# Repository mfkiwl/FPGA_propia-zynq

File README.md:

# FPGA_propia
 En este repositorio se subirán los ficheros que permitirán crear una FPGA basada en Zynq-7000

Todo el desarrollo está hecho con KiCad (software libre) para que cualquiera pueda replicarla o mejorarla a su gusto con los ficheros que se van a publicar

## Libreria
El fichero tiene una librería llamada 'Zynq-7000' en la que está el symbol de un XC7Z010 del cual se implementará la versión CLG400 (400 pines en formato de soldadura BGA) 
## XC7Z010
El símbolo consta de 9 partes, de las que se va a describir su selección a continuación
### - _Símbolo A_

En este símbolo se reflejan los pines de referencia, además de los pines de depuración TMS, TCK, TDI y TDO. Estos pines pueden necesitar de un cable depurar para cargar el programa o de un USB OTG, que permita evitar tener que usar un cable depurador.

### - _Símbolo B_

En este símbolo se reflejan los pines que no tienen conexión

### - _Símbolo c_

En este símbolo se reflejan los pines de entrada/salida que se podrán configurar como se quiera

### - _Símbolo D_

En este símbolo se reflejan los pines de entrada/salida que se podrán configurar como se quiera

### - _Símbolo E_

En este símbolo se reflejan los pines que van a ir a la/las memoria ram. A los pines de la ram se pueden unir varias memorias para aumentar su tamaño.

### - _Símbolo F_

En este símbolo se reflejan los pines MIO

### - _Símbolo G_

En este símbolo se reflejan los pines MIO continuación de los anteriores

### - _Símbolo H_

En este símbolo se reflejan las alimentaciones de cada parte del integrado. Hay que tener en cuenta que cada parte tiene una alimentación distinta, la VCCO_BRAM y los VCCO_PINT de 1V, los VCCO_MIO 3.3V, los VCCO_DDR de 1.35V y los VCCAUX y los VCCPAUX de 1.8V

### - _Símbolo I_

En este símbolo se reflejan las masas de todo el integrado. Todas las masas van unidas a mismo punto.

### - *Formato del integrado*

En esta imagen se refleja como es el integrado CLG400 de 400 pines(20x20) para BGA

*** Toda la documentación del frabicante se puede obtener del siguiente enlace: ***
https://www.xilinx.com/support/documentation/user_guides/ug865-Zynq-7000-Pkg-Pinout.pdf

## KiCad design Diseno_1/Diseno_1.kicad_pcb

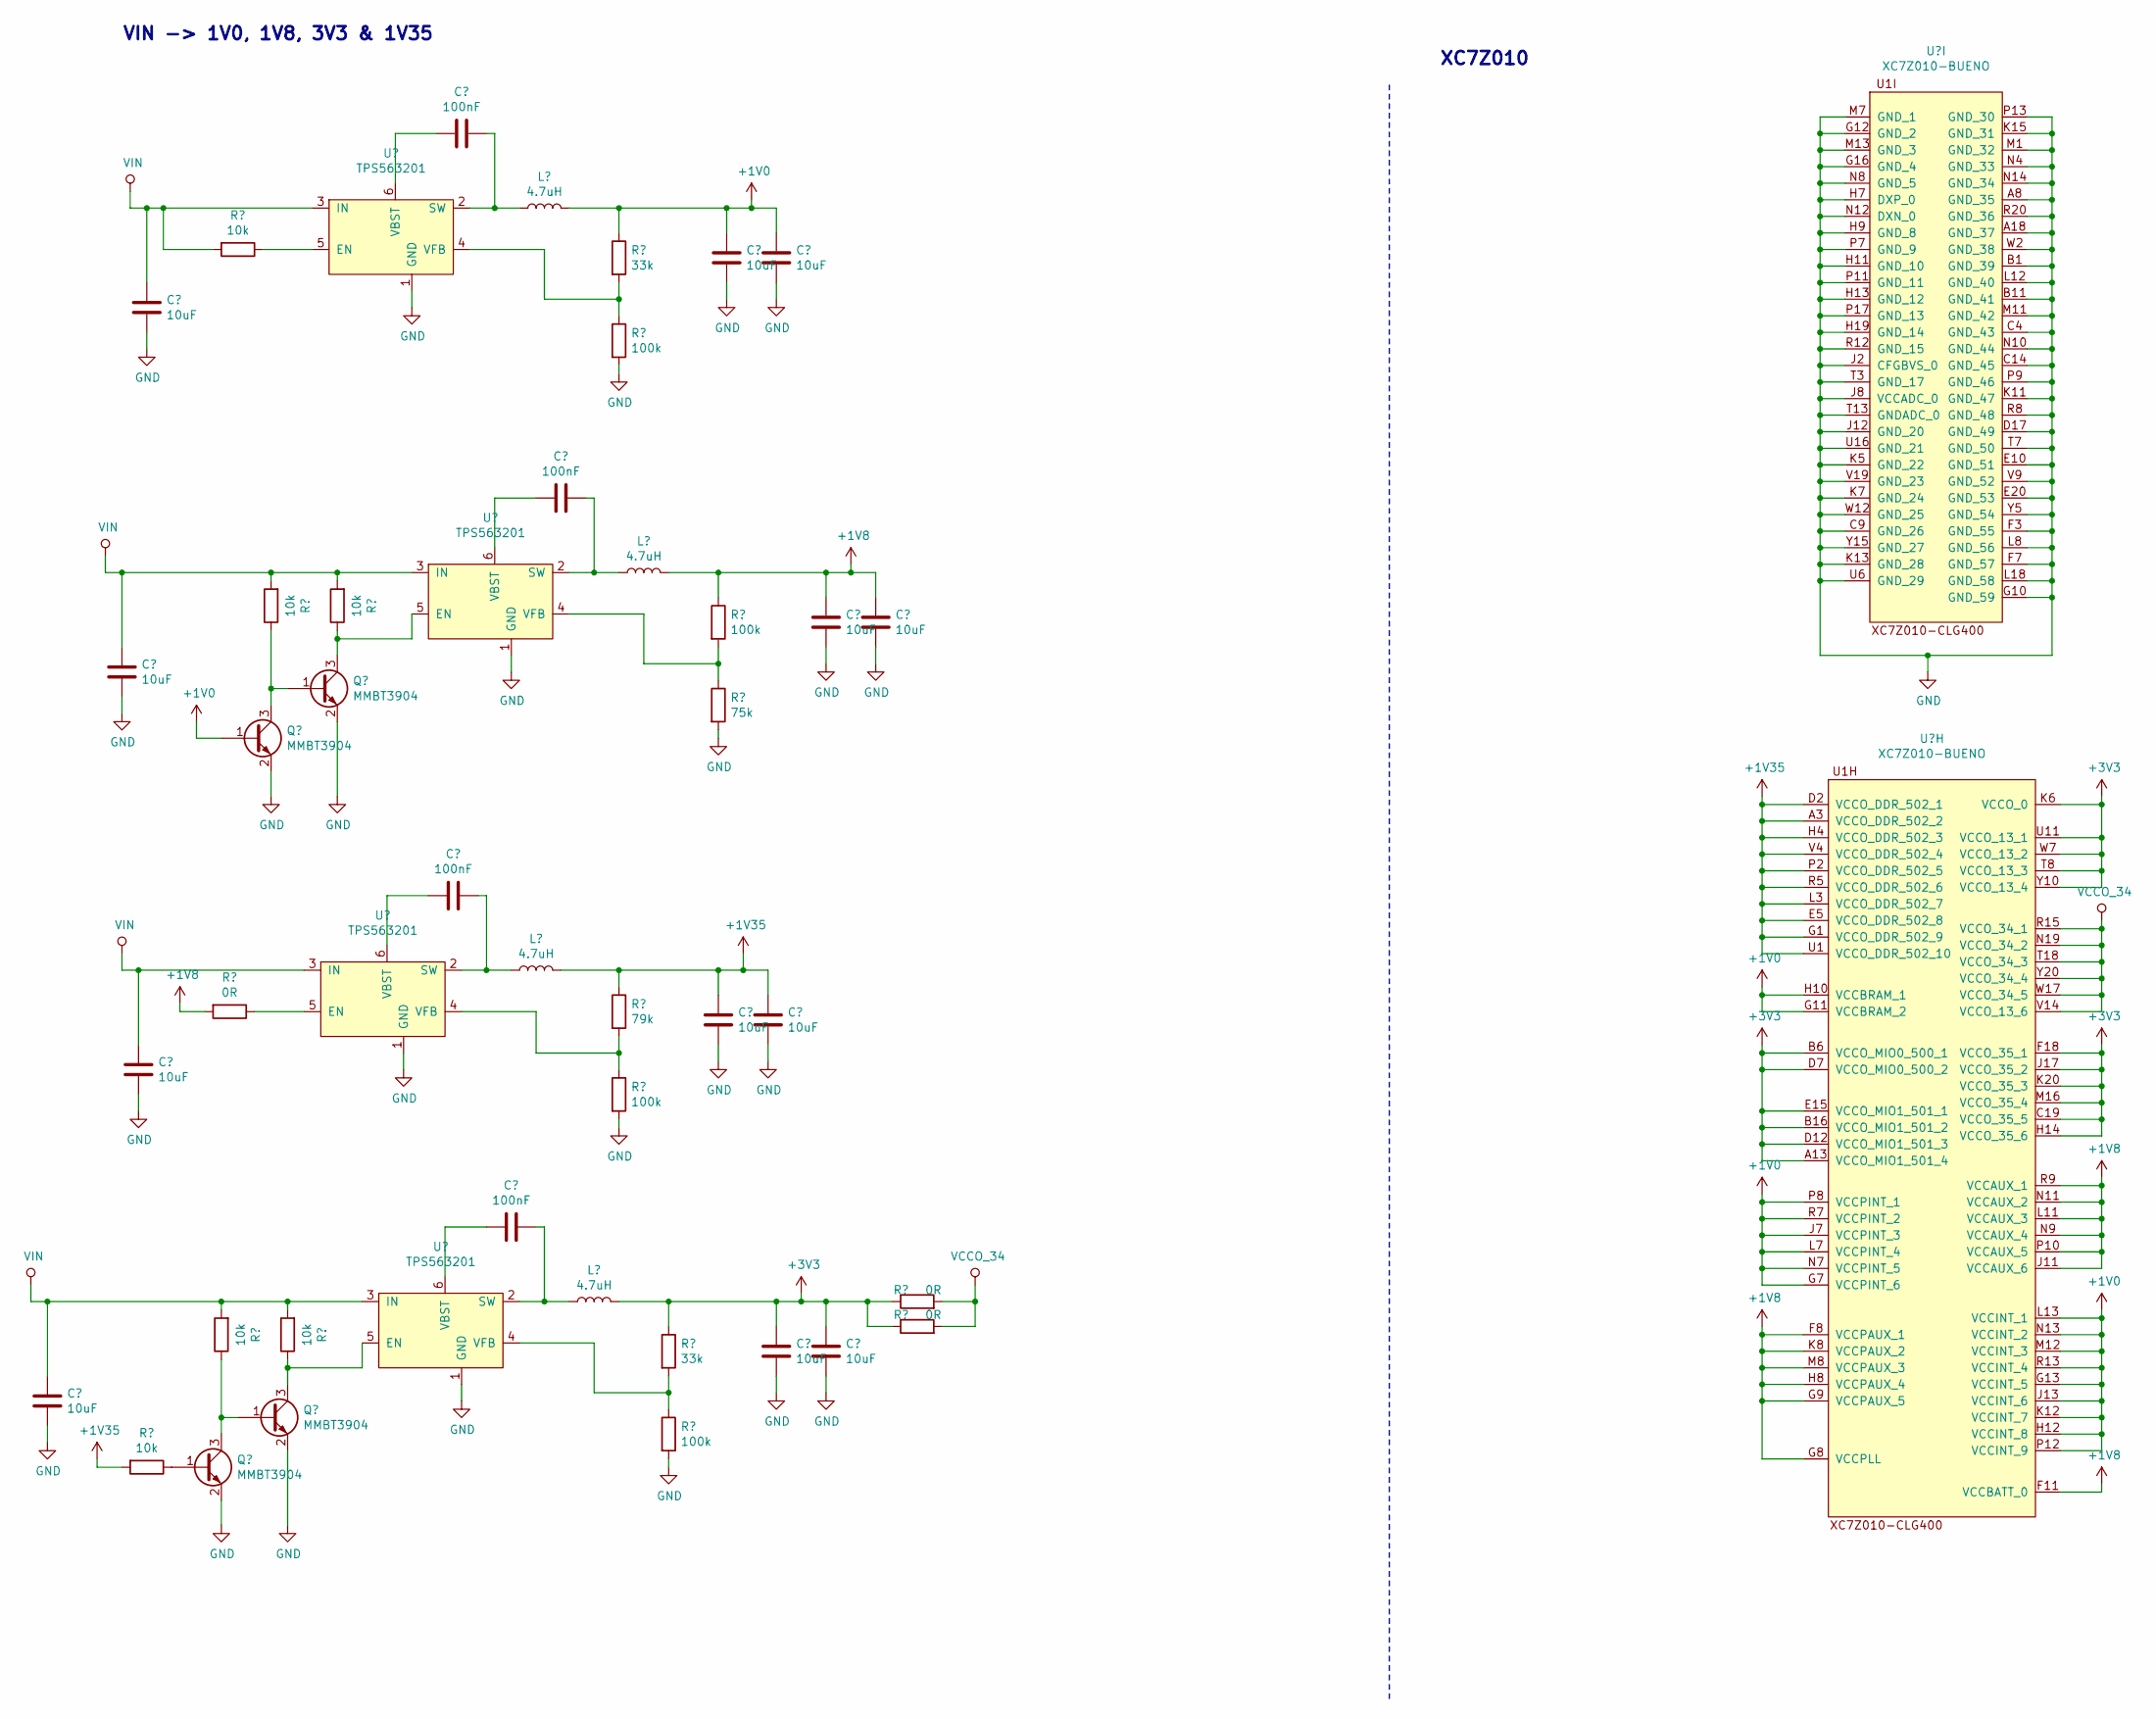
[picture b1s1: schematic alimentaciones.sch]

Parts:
C1, C2, C3, C4, C9, C10, C11, C12, C13, C14, C15, C16: 10uF; C_0805_2012Metric
C5, C6, C7, C8: 100nF; C_0805_2012Metric
L1, L2, L3, L4: 4.7uH; L_0805_2012Metric
Q1, Q2, Q3, Q4: MMBT3904; SOT-23
R1, R2, R4, R5, R6, R7: 10k; R_0805_2012Metric
R3, R16, R17: 0R; R_0805_2012Metric
R8, R12: 33k; R_0805_2012Metric
R9, R11, R13, R14: 100k; R_0805_2012Metric
R10: 79k; R_0805_2012Metric
R15: 75k; R_0805_2012Metric
U1, U2, U3, U4: TPS563201
U5: XC7Z010-BUENO; BGA-400_20x20_17.0x17.0mm

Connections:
+1V0: C10.1, C12.1, L2.2, Q2.1 (B), R8.1, U5.G7 (VCCPINT_6), U5.G11 (VCCBRAM_2), U5.G13 (VCCINT_5), U5.H10 (VCCBRAM_1), U5.H12 (VCCINT_8), U5.J7 (VCCPINT_3), U5.J13 (VCCINT_6), U5.K12 (VCCINT_7), U5.L7 (VCCPINT_4), U5.L13 (VCCINT_1), U5.M12 (VCCINT_3), U5.N7 (VCCPINT_5), U5.N13 (VCCINT_2), U5.P8 (VCCPINT_1), U5.P12 (VCCINT_9), U5.R7 (VCCPINT_2), U5.R13 (VCCINT_4)
+1V8: C14.1, C16.1, L4.2, R3.2, R14.1, U5.F8 (VCCPAUX_1), U5.F11 (VCCBATT_0), U5.G8 (VCCPLL), U5.G9 (VCCPAUX_5), U5.H8 (VCCPAUX_4), U5.J11 (VCCAUX_6), U5.K8 (VCCPAUX_2), U5.L11 (VCCAUX_3), U5.M8 (VCCPAUX_3), U5.N9 (VCCAUX_4), U5.N11 (VCCAUX_2), U5.P10 (VCCAUX_5), U5.R9 (VCCAUX_1); also elsewhere on the board
+1V35: C9.1, C11.1, L1.2, R1.2, R10.1, U5.A3 (VCCO_DDR_502_2), U5.D2 (VCCO_DDR_502_1), U5.E5 (VCCO_DDR_502_8), U5.G1 (VCCO_DDR_502_9), U5.H4 (VCCO_DDR_502_3), U5.L3 (VCCO_DDR_502_7), U5.P2 (VCCO_DDR_502_5), U5.R5 (VCCO_DDR_502_6), U5.U1 (VCCO_DDR_502_10), U5.V4 (VCCO_DDR_502_4); also elsewhere on the board
/Entradas y Salidas/BANK34_N17: U5.N17 (IO_L23P_T3_34); also elsewhere on the board
/Entradas y Salidas/BANK34_N18: U5.N18 (IO_L13P_T2_MRCC_34); also elsewhere on the board
/Entradas y Salidas/BANK34_N20: U5.N20 (IO_L14P_T2_SRCC_34); also elsewhere on the board
/Entradas y Salidas/BANK34_P14: U5.P14 (IO_L6P_T0_34); also elsewhere on the board
/Entradas y Salidas/BANK34_P15: U5.P15 (IO_L24P_T3_34); also elsewhere on the board
/Entradas y Salidas/BANK34_P16: U5.P16 (IO_L24N_T3_34); also elsewhere on the board
/Entradas y Salidas/BANK34_P18: U5.P18 (IO_L23N_T3_34); also elsewhere on the board
/Entradas y Salidas/BANK34_P19: U5.P19 (IO_L13N_T2_MRCC_34); also elsewhere on the board
/Entradas y Salidas/BANK34_P20: U5.P20 (IO_L14N_T2_SRCC_34); also elsewhere on the board
/Entradas y Salidas/BANK34_R14: U5.R14 (IO_L6N_T0_VREF_34); also elsewhere on the board
/Entradas y Salidas/BANK34_R16: U5.R16 (IO_L19P_T3_34); also elsewhere on the board
/Entradas y Salidas/BANK34_R17: U5.R17 (IO_L19N_T3_VREF_34); also elsewhere on the board
/Entradas y Salidas/BANK34_R18: U5.R18 (IO_L20N_T3_34); also elsewhere on the board
/Entradas y Salidas/BANK34_R19: U5.R19 (IO_0_34); also elsewhere on the board
/Entradas y Salidas/BANK34_T10: U5.T10 (IO_L1N_0_34); also elsewhere on the board
/Entradas y Salidas/BANK34_T11: U5.T11 (IO_L1P_T0_34); also elsewhere on the board
/Entradas y Salidas/BANK34_T12: U5.T12 (IO_L2P_T0_34); also elsewhere on the board
/Entradas y Salidas/BANK34_T14: U5.T14 (IO_l5P_T0_34); also elsewhere on the board
/Entradas y Salidas/BANK34_T15: U5.T15 (IO_L5N_T0_34); also elsewhere on the board
/Entradas y Salidas/BANK34_T16: U5.T16 (IO_L9P_T1_DQS_34); also elsewhere on the board
/Entradas y Salidas/BANK34_T17: U5.T17 (IO_L20P_T3_34); also elsewhere on the board
/Entradas y Salidas/BANK34_T19: U5.T19 (IO_25_34); also elsewhere on the board
/Entradas y Salidas/BANK34_T20: U5.T20 (IO_L15P_T2_DQS_34); also elsewhere on the board
/Entradas y Salidas/BANK34_U12: U5.U12 (IO_L2N_T0_34); also elsewhere on the board
/Entradas y Salidas/BANK34_U14: U5.U14 (IO_L11P_T1_SRCC_34); also elsewhere on the board
/Entradas y Salidas/BANK34_U15: U5.U15 (IO_L11N_T1_SRCC_34); also elsewhere on the board
/Entradas y Salidas/BANK34_U17: U5.U17 (IO_L9N_T1_DQS_34); also elsewhere on the board
/Entradas y Salidas/BANK34_U18: U5.U18 (IO_L12P_T1_MRCC_34); also elsewhere on the board
/Entradas y Salidas/BANK34_U19: U5.U19 (IO_L12N_T1_MRCC_34); also elsewhere on the board
/Entradas y Salidas/BANK34_U20: U5.U20 (IO_L5N_T2_DQS_34); also elsewhere on the board
/Entradas y Salidas/BANK34_V12: U5.V12 (IO_L4P_T0_34); also elsewhere on the board
/Entradas y Salidas/BANK34_V13: U5.V13 (IO_L3N_T0_DQS_34); also elsewhere on the board
/Entradas y Salidas/BANK34_V15: U5.V15 (IO_L10P_T1_34); also elsewhere on the board
/Entradas y Salidas/BANK34_V16: U5.V16 (IO_L18P_T2_34); also elsewhere on the board
/Entradas y Salidas/BANK34_V17: U5.V17 (IO_L21P_T3_VREF_34); also elsewhere on the board
/Entradas y Salidas/BANK34_V18: U5.V18 (IO_L21N_T3_DQS_34); also elsewhere on the board
/Entradas y Salidas/BANK34_V20: U5.V20 (IO_L6P_T2_34); also elsewhere on the board
/Entradas y Salidas/BANK34_W13: U5.W13 (IO_L4N_T0_34); also elsewhere on the board
/Entradas y Salidas/BANK34_W14: U5.W14 (IO_L8P_T1_34); also elsewhere on the board
/Entradas y Salidas/BANK34_W15: U5.W15 (IO_L10N_T1_34); also elsewhere on the board
/Entradas y Salidas/BANK34_W16: U5.W16 (IO_L18N_T2_34); also elsewhere on the board
/Entradas y Salidas/BANK34_W18: U5.W18 (IO_L22P_T3_34); also elsewhere on the board
/Entradas y Salidas/BANK34_W19: U5.W19 (IO_L22N_T3_34); also elsewhere on the board
/Entradas y Salidas/BANK34_W20: U5.W20 (IO_L6N_T2_34); also elsewhere on the board
/Entradas y Salidas/BANK34_Y14: U5.Y14 (IO_L8N_T1_34); also elsewhere on the board
/Entradas y Salidas/BANK34_Y16: U5.Y16 (IO_L7P_T1_34); also elsewhere on the board
/Entradas y Salidas/BANK34_Y17: U5.Y17 (IO_L7N_T1_34); also elsewhere on the board
/Entradas y Salidas/BANK34_Y18: U5.Y18 (IO_L17P_T2_34); also elsewhere on the board
/Entradas y Salidas/BANK34_Y19: U5.Y19 (IO_L17N_T2_34); also elsewhere on the board
/Entradas y Salidas/BANK35_A20: U5.A20 (IO_L2N_T0_AD8N_35); also elsewhere on the board
/Entradas y Salidas/BANK35_B19: U5.B19 (IO_L2P_T0_AD8P_35); also elsewhere on the board
/Entradas y Salidas/BANK35_B20: U5.B20 (IO_L1N_T0_AD0P_35); also elsewhere on the board
/Entradas y Salidas/BANK35_C20: U5.C20 (IO_L1P_T0_AD0P_35); also elsewhere on the board
/Entradas y Salidas/BANK35_D18: U5.D18 (IO_L3N_T0_DQS_AD1N_35); also elsewhere on the board
/Entradas y Salidas/BANK35_D19: U5.D19 (IO_L4P_T0_35); also elsewhere on the board
/Entradas y Salidas/BANK35_D20: U5.D20 (IO_L4N_T0_35); also elsewhere on the board
/Entradas y Salidas/BANK35_E17: U5.E17 (IO_L3P_T0_DQS_AD1P_35); also elsewhere on the board
/Entradas y Salidas/BANK35_E18: U5.E18 (IO_L5P_T0_AD9P_35); also elsewhere on the board
/Entradas y Salidas/BANK35_E19: U5.E19 (IO_L5N_T0_AD9N_35); also elsewhere on the board
/Entradas y Salidas/BANK35_F16: U5.F16 (IO_L6P_T0_35); also elsewhere on the board
/Entradas y Salidas/BANK35_F17: U5.F17 (IO_L6N_T0_VREF_35); also elsewhere on the board
/Entradas y Salidas/BANK35_F19: U5.F19 (IO_L15P_T2_DQS_AD12P_35); also elsewhere on the board
/Entradas y Salidas/BANK35_F20: U5.F20 (IO_L15N_T2_DQS_AD12N_35); also elsewhere on the board
/Entradas y Salidas/BANK35_G14: U5.G14 (IO_0_35); also elsewhere on the board
/Entradas y Salidas/BANK35_G15: U5.G15 (IO_L19N_T3_VREF_35); also elsewhere on the board
/Entradas y Salidas/BANK35_G17: U5.G17 (IO_L16P_T2_35); also elsewhere on the board
/Entradas y Salidas/BANK35_G18: U5.G18 (IO_L16N_T2_35); also elsewhere on the board
/Entradas y Salidas/BANK35_G19: U5.G19 (IO_L18P_T2_AD13P_35); also elsewhere on the board
/Entradas y Salidas/BANK35_G20: U5.G20 (IO_L18N_T2_AD13N_35); also elsewhere on the board
/Entradas y Salidas/BANK35_H15: U5.H15 (IO_L19P_T3_35); also elsewhere on the board
/Entradas y Salidas/BANK35_H16: U5.H16 (IO_L13P_T2_MRCC_35); also elsewhere on the board
/Entradas y Salidas/BANK35_H17: U5.H17 (IO_L13N_T2_MRCC_35); also elsewhere on the board
/Entradas y Salidas/BANK35_H18: U5.H18 (IO_L14N_T2_AD4N_SRCC_35); also elsewhere on the board
/Entradas y Salidas/BANK35_H20: U5.H20 (IO_L17N_T2_AD5N_35); also elsewhere on the board
/Entradas y Salidas/BANK35_J14: U5.J14 (IO_L20N_T3_AD6N_35); also elsewhere on the board
/Entradas y Salidas/BANK35_J15: U5.J15 (IO_25_35); also elsewhere on the board
/Entradas y Salidas/BANK35_J16: U5.J16 (IO_L24N_T3_AD15N_35); also elsewhere on the board
/Entradas y Salidas/BANK35_J18: U5.J18 (IO_L14P_T2_AD4P_SRCC_35); also elsewhere on the board
/Entradas y Salidas/BANK35_J19: U5.J19 (IO_L10N_AD11N_35); also elsewhere on the board
/Entradas y Salidas/BANK35_J20: U5.J20 (IO_L17P_T2_AD5P_35); also elsewhere on the board
/Entradas y Salidas/BANK35_K14: U5.K14 (IO_L20P_T3_AD6P_35); also elsewhere on the board
/Entradas y Salidas/BANK35_K16: U5.K16 (IO_L24P_T3_AD15P_35); also elsewhere on the board
/Entradas y Salidas/BANK35_K17: U5.K17 (IO_L12P_T1_MRCC_35); also elsewhere on the board
/Entradas y Salidas/BANK35_K18: U5.K18 (IO_L12N_T1_MRCC_35); also elsewhere on the board
/Entradas y Salidas/BANK35_K19: U5.K19 (IO_L10P_T1_AD11P_35); also elsewhere on the board
/Entradas y Salidas/BANK35_L14: U5.L14 (IO_L22P_T3_AD7P_35); also elsewhere on the board
/Entradas y Salidas/BANK35_L15: U5.L15 (IO_L22N_T3_AD7N_35); also elsewhere on the board
/Entradas y Salidas/BANK35_L16: U5.L16 (IO_L11P_T1_SRCC_35); also elsewhere on the board
/Entradas y Salidas/BANK35_L17: U5.L17 (IO_L11N_T1_SRCC_35); also elsewhere on the board
/Entradas y Salidas/BANK35_L19: U5.L19 (IO_L9P_T1_DQS_AD3P_35); also elsewhere on the board
/Entradas y Salidas/BANK35_L20: U5.L20 (IO_L9N_T1_DQS_AD3N_35); also elsewhere on the board
/Entradas y Salidas/BANK35_M14: U5.M14 (IO_L23P_T3_35); also elsewhere on the board
/Entradas y Salidas/BANK35_M15: U5.M15 (IO_L23N_T3_35); also elsewhere on the board
/Entradas y Salidas/BANK35_M17: U5.M17 (IO_L8P_T1_AD10P_35); also elsewhere on the board
/Entradas y Salidas/BANK35_M18: U5.M18 (IO_L8N_T1_AD10N_35); also elsewhere on the board
/Entradas y Salidas/BANK35_M19: U5.M19 (IO_L7P_T1_AD2P_35); also elsewhere on the board
/Entradas y Salidas/BANK35_M20: U5.M20 (IO_L7N_T1_AD2N_35); also elsewhere on the board
/Entradas y Salidas/BANK35_N15: U5.N15 (IO_L21P_T3_DQS_AD14P_35); also elsewhere on the board
/Entradas y Salidas/BANK35_N16: U5.N16 (IO_L21N_T3_DQS_AD14N_35); also elsewhere on the board
GND: C1.2, C2.2, C3.2, C4.2, C9.2, C10.2, C11.2, C12.2, C13.2, C14.2, C15.2, C16.2, Q1.2 (E), Q2.2 (E), Q3.2 (E), Q4.2 (E), R9.2, R11.2, R13.2, R15.2, U1.1 (GND), U2.1 (GND), U3.1 (GND), U4.1 (GND), U5.A8 (GND_35), U5.A18 (GND_37), U5.B1 (GND_39), U5.B11 (GND_41), U5.C4 (GND_43), U5.C9 (GND_26), U5.C14 (GND_45), U5.D17 (GND_49), U5.E10 (GND_51), U5.E20 (GND_53), U5.F3 (GND_55), U5.F7 (GND_57), U5.G10 (GND_59), U5.G12 (GND_2), U5.G16 (GND_4), U5.H7 (DXP_0), U5.H9 (GND_8), U5.H11 (GND_10), U5.H13 (GND_12), U5.H19 (GND_14), U5.J2 (CFGBVS_0), U5.J8 (VCCADC_0), U5.J12 (GND_20), U5.K5 (GND_22), U5.K7 (GND_24), U5.K11 (GND_47), U5.K13 (GND_28), U5.K15 (GND_31), U5.L8 (GND_56), U5.L12 (GND_40), U5.L18 (GND_58), U5.M1 (GND_32), U5.M7 (GND_1), U5.M11 (GND_42), U5.M13 (GND_3), U5.N4 (GND_33), U5.N8 (GND_5), U5.N10 (GND_44), U5.N12 (DXN_0), U5.N14 (GND_34), U5.P7 (GND_9), U5.P9 (GND_46), U5.P11 (GND_11), U5.P13 (GND_30), U5.P17 (GND_13), U5.R8 (GND_48), U5.R12 (GND_15), U5.R20 (GND_36), U5.T3 (GND_17), U5.T7 (GND_50), U5.T13 (GNDADC_0), U5.U6 (GND_29), U5.U13 (IO_L3P_T0_DQS_PUDC_B_34), U5.U16 (GND_21), U5.V9 (GND_52), U5.V19 (GND_23), U5.W2 (GND_38), U5.W12 (GND_25), U5.Y5 (GND_54), U5.Y15 (GND_27); also elsewhere on the board
unnamed: C5.1, L1.1, U1.2 (SW)
unnamed: C5.2, U1.6 (VBST)
unnamed: C6.1, L2.1, U2.2 (SW)
unnamed: C6.2, U2.6 (VBST)
unnamed: C7.1, L3.1, U3.2 (SW)
unnamed: C7.2, U3.6 (VBST)
unnamed: C8.1, L4.1, U4.2 (SW)
unnamed: C8.2, U4.6 (VBST)
unnamed: Q1.1 (B), R1.1
unnamed: Q1.3 (C), Q3.1 (B), R2.1
unnamed: Q2.3 (C), Q4.1 (B), R5.1
unnamed: Q3.3 (C), R6.1, U3.5 (EN)
unnamed: Q4.3 (C), R7.1, U4.5 (EN)
unnamed: R3.1, U1.5 (EN)
unnamed: R4.1, U2.5 (EN)
unnamed: R8.2, R9.1, U2.4 (VFB)
unnamed: R10.2, R11.1, U1.4 (VFB)
unnamed: R12.2, R13.1, U3.4 (VFB)
unnamed: R14.2, R15.1, U4.4 (VFB)

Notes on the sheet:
VIN -> 1V0, 1V8, 3V3 & 1V35
XC7Z010
